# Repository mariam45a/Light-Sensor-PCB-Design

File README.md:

# Light-Sensor-PCB-Design
Implemented and developed a light sensor PCB using KiCad, from the circuit schematic to the PCB layout. Executed PCB layout with efficient component placement and routing, leading to a functional and manufacturable design.

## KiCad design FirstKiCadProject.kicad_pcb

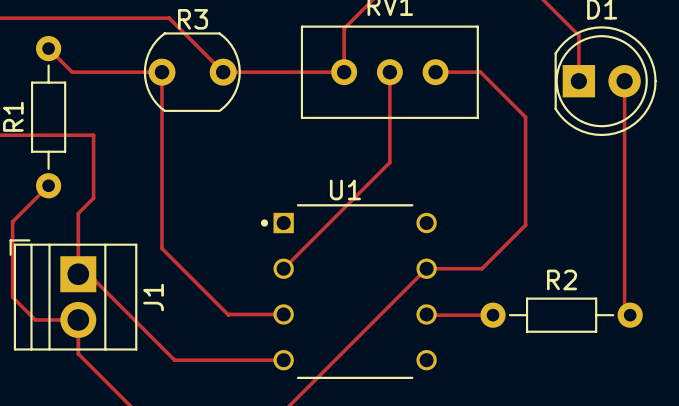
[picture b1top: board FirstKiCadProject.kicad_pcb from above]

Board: 2 copper layers, 7 parts (0 on the bottom side), 6 nets.

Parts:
D1: LED; LED_D5.0mm
J1: Screw_Terminal_01x02 (9 Volts); TerminalBlock_Xinya_XY308-2.54-2P_1x02_P2.54mm_Horizontal
R1, R2: R; R_Axial_DIN0204_L3.6mm_D1.6mm_P7.62mm_Horizontal
R3: LDR07; R_LDR_5.1x4.3mm_P3.4mm_Vertical
RV1: R_Potentiometer; Potentiometer_Bourns_3296W_Vertical
U1: LM741

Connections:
unnamed: D1.2 (A), R2.2
unnamed: D1.1 (K), J1.1, R3.2, RV1.3, U1.4 (V-)
unnamed: J1.2, R1.1, RV1.1, U1.7 (V+)
unnamed: R2.1, U1.6
unnamed: R1.2, R3.1, U1.3 (+)
unnamed: RV1.2, U1.2 (-)
